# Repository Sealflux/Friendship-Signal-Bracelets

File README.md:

# Friendship-Signal-Bracelets
Friendship Signal Bracelets, which as the name suggests, light up when a bestie is nearby.
## Built for Macondo Hack Club
# Description
Two (or more) bracelets that light up, vibrate, and/or display a pattern when they come within ~3-5 meters of each other, using BLE (Bluetooth Low Energy) RSSI-based proximity detection.

## Features
- Proximity Detection - BLE RSSI(Bluetooth Low Energy Received Signal Strength Indicator) to detect nearby besties
- Cool lights(6 LEDs) when your bestie is nearby
- OLED Display(You can see which bestie is nearby!)
- Audio beeping(Buzzer) when your friend is nearby
- Microphone

## Hardware
- Seeed Xiao ESP32-C3
- SSD1306 0.96" OLED
- WS2812B-V6 LEDs
- ICS-43434 Mems Microphone
- ISM303DACTR Accelerometer
- SPX3819M5-L-1-8 LDO
- LSF0108PWR Level Shifter
- 250mAh LiPo Battery

## Bill of Materials (BOM)

| Designator | Part | Qty | Cost (each) | Total | Link | LCSC # |
|------------|------|:---:|------------|-------|------|--------|
| U1 | Seeed Xiao ESP32-C3 | 1 | $4.99 | $4.99 | https://www.seeedstudio.com/Seeed-XIAO-ESP32C3-p-5431.html | N/A |
| U2 | SSD1306 0.96" OLED | 1 | $2.24 | $2.24 | https://www.lcsc.com/product-detail/C5248080.html | C5248080 |
| SW1 | Tactile Push Button | 1 | $0.56 | $0.56 | https://www.lcsc.com/product-detail/C2888493.html | C2888493 |
| BT1 | LiPo 250mAh Battery | 1 | $8.99 | $8.99 | https://www.amazon.com/EEMB-Battery-Rechargeable-Lithium-Connector/dp/B08FD3V6TF | N/A |
| PCB | PCB Board | 5 | $0.80 | $4 | https://www.jlcpcb.com | N/A |
| C1,C2,C3 | 100nF Capacitor | 3 | $0.0086 | $0.86(Min order of 100) | https://www.lcsc.com/product-detail/C60474.html | C60474 |
| C4 | 220nF Capacitor | 1 | $0.0238 | $1.19(Min order of 100) | https://www.lcsc.com/product-detail/C64705.html | C64705 |
| C5 | 10µF Capacitor | 1 | $0.0372 | $0.74(Min order of 20) | https://www.lcsc.com/product-detail/C192100.html | C192100 |
| C6 | 10nF Capacitor | 1 | $0.016 | $0.8(Min order of 50)| https://www.lcsc.com/product-detail/C100042.html | C100042 |
| LED1-6 | WS2812B-V6 LED | 6 | $0.1011 | $1.01(Multiple order of 5s) | https://www.lcsc.com/product-detail/C52917433.html | C52917433 |
| R1 | 100kΩ Resistor | 1 | $0.0061 | $0.62(Min order of 100) | https://www.lcsc.com/product-detail/C60491.html | C60491 |
| U3 | ICS-43434 Microphone | 1 | $4.66 | $4.66 | https://www.lcsc.com/product-detail/C5656610.html | C5656610 |
| U4 | ISM303DACTR Accelerometer | 1 | $4.04 | $4.04 | https://www.lcsc.com/product-detail/C2913653.html | C2913653 |
| U5 | SPX3819M5-L-1-8 Voltage Regulator | 1 | $0.1437 | $0.72(Min order of 5) | https://www.lcsc.com/product-detail/C24639.html | C24639 |
| U6 | LSF0108PWR Level Shifter | 1 | $0.5849 | $0.5849 | https://www.lcsc.com/product-detail/C190219.html | C190219 |
| BUZZER1 | 1207-P6.5MM Buzzer | 1 | $0.0317 | $0.32(Min order of 10) | https://www.lcsc.com/product-detail/C49246964.html | C49246964 |
| Shipping | N/A | 1 | Seeed($6.5) + LCSC($9.58) + Amazon($7.95) + JLCPCB($3.12) | N/A | N/A | N/A
| Total Costs | N/A | 1 | 11.49+16.94+7.12+27.98 | $63.53 | N/A | N/A |

## Firmware
Basic functional firmware in `/firmware/friendship_bracelet.ino`.
## Steps To Reproduce
1. Order all the components from the BOM
2. Download the gerbers.zip from Production folder and order a pcb from whatever manufacturer(JLCPCB)
3. Solder the components onto the PCB
4. Download the enclosure from Production folder and print using PETG or TPU
5. Order watch strap adapters
6. Assemble the case, sand down the bottom and top parts and hot glue the together. The PCB will fit snugly
7. Flash the Firmware onto the PCB
8. Now repeat steps 1 and 7 for a second bracelet
9. Enjoy!

## Schematic

## PCB

## PCBA

## Case

## Demo Video

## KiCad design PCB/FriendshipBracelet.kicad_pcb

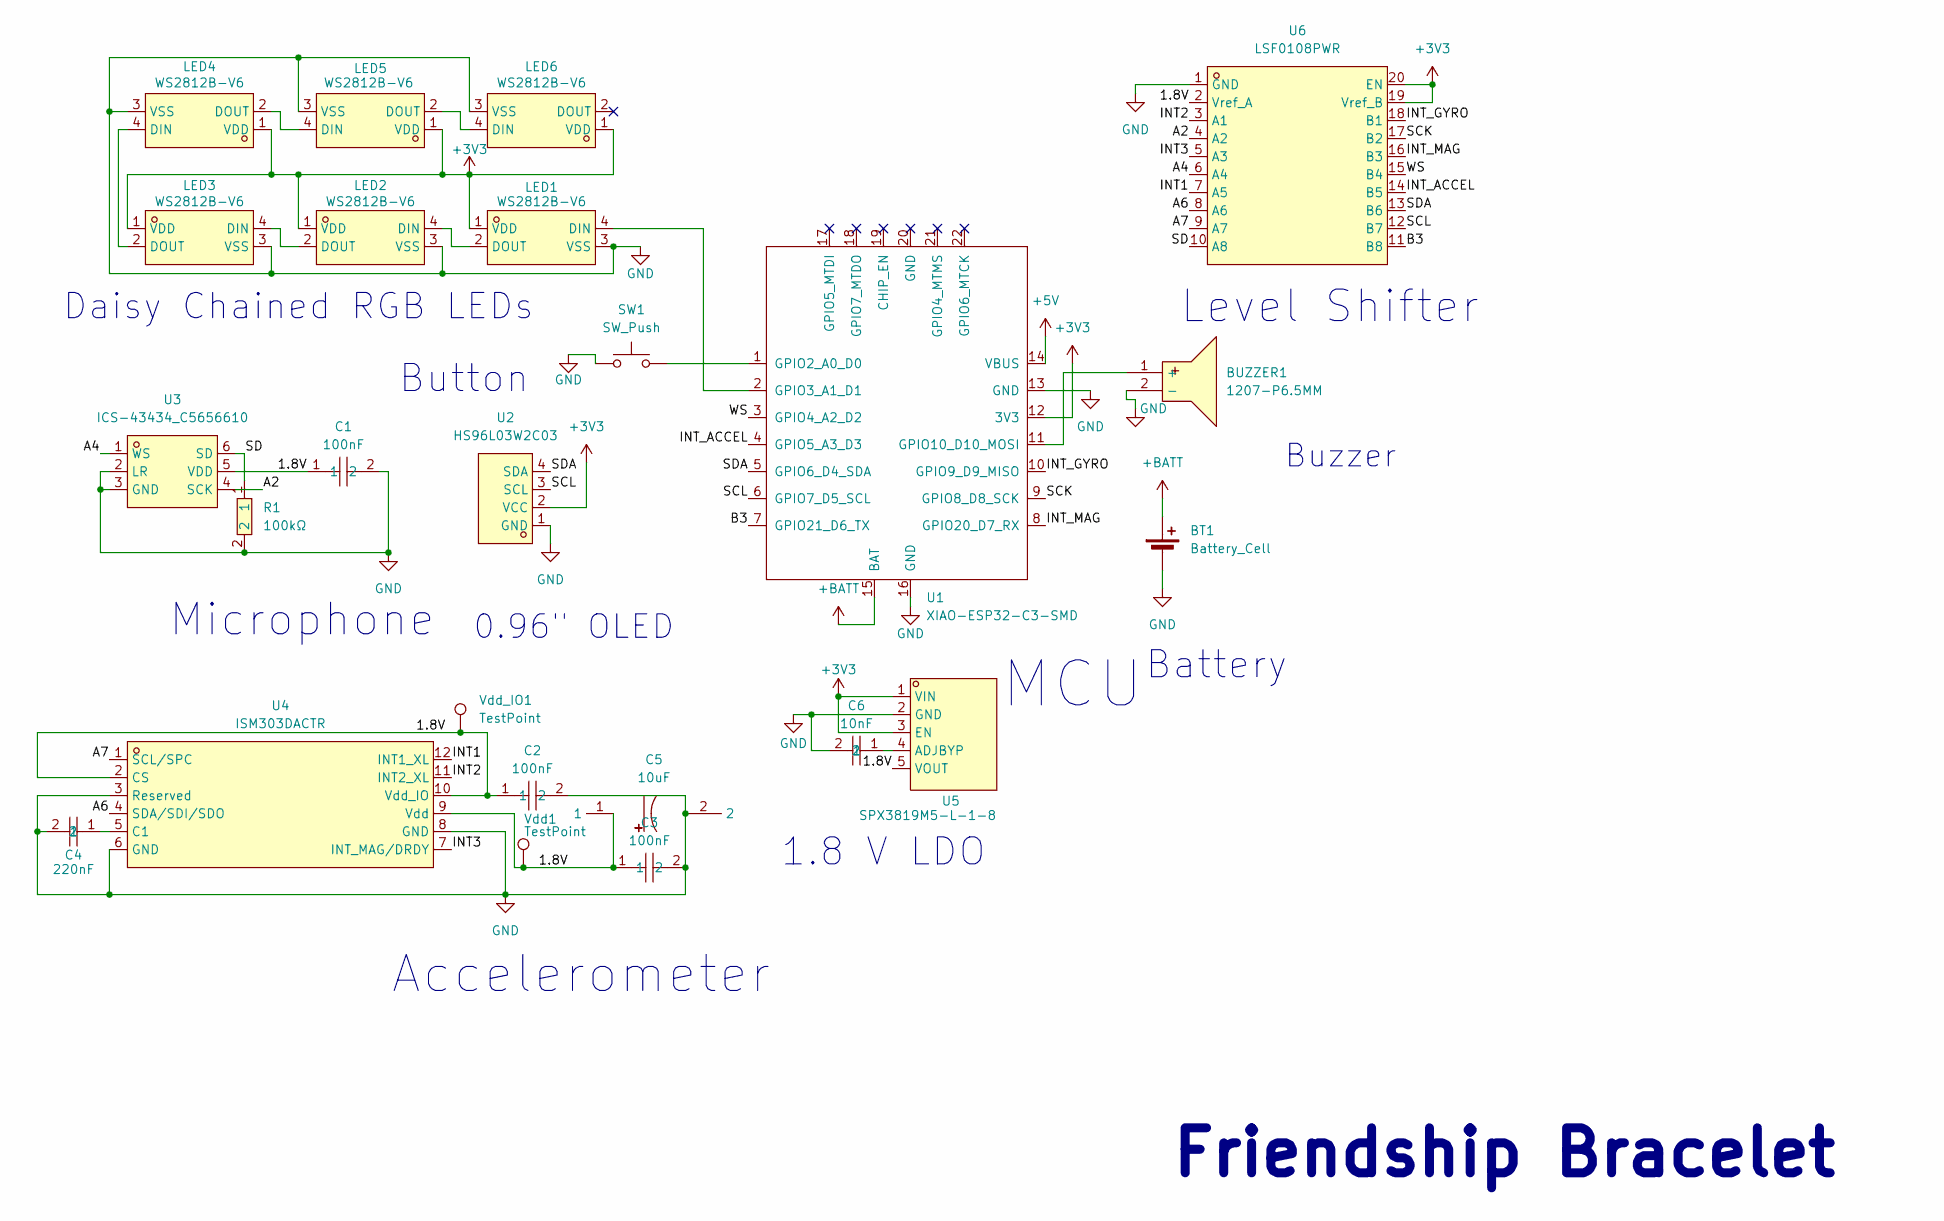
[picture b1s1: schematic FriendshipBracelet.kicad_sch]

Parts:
BT1: Battery_Cell; PinHeader_1x02_P2.54mm_Vertical
BUZZER1: 1207-P6.5MM; BUZ-TH_BD12.5-P6.50-D1.4; MPN 1207-P6.5MM; LCSC Part C49246964
C1, C2, C3: 100nF; C0402; MPN CC0402KRX7R7BB104; LCSC Part C60474
C4: 220nF; C0603; MPN CL10B224KB8NNNC; LCSC Part C64705
C5: 10uF; CAP-TH_BD5.0-P2.00-D0.8-FD; MPN ECR1HBK100MLL050011; LCSC Part C192100
C6: 10nF; C0603; MPN CC0603KRX7R9BB103; LCSC Part C100042
LED1, LED2, LED3, LED4, LED5, LED6: WS2812B-V6; LED-SMD_4P-L5.0-W5.0-TL-A; MPN WS2812B-V6; LCSC Part C52917433
R1: 100kΩ; R0402; MPN RC0402FR-07100KL; LCSC Part C60491
SW1: SW_Push; SW-TH_4P-L4.5-W4.5-P3.00-LS4.8
U1: XIAO-ESP32-C3-SMD; XIAO-ESP32-C3-DIP-SMD
U2: HS96L03W2C03; OLED-TH_L27.8-W27.2-P2.54_C9900033791; MPN HS96L03W2C03; LCSC Part C5248080
U3: ICS-43434_C5656610; MIC-SMD_6P-L3.5-W2.7-P0.90-BL; MPN ICS-43434; LCSC Part C5656610
U4: ISM303DACTR; VLGA-12_L2.0-W2.0-P0.50-BL; MPN ISM303DACTR; LCSC Part C2913653
U5: SPX3819M5-L-1-8; SOT-23-5_L3.0-W1.7-P0.95-LS2.8-TL; MPN SPX3819M5-L-1-8/TR; LCSC Part C24639
U6: LSF0108PWR; TSSOP-20_L6.5-W4.4-P0.65-LS6.4-BL; MPN LSF0108PWR; LCSC Part C190219
Vdd1: TestPoint; TestPoint_Pad_D2.5mm
Vdd_IO1: TestPoint; TestPoint_Pad_D2.5mm

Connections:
+3V3: LED1.1 (VDD), LED2.1 (VDD), LED3.1 (VDD), LED4.1 (VDD), LED5.1 (VDD), LED6.1 (VDD), U1.12 (3V3), U2.2 (VCC), U5.1 (VIN), U5.3 (EN), U6.19 (Vref_B), U6.20 (EN)
+5V: U1.14 (VBUS)
+BATT: BT1.1 (+), U1.15 (BAT)
/1.8V: C1.1, C2.1, C3.1, C5.1, U3.5 (VDD), U4.2 (CS), U4.9 (Vdd), U4.10 (Vdd_IO), U5.5 (VOUT), U6.2 (Vref_A), Vdd1.1 (1_1), Vdd_IO1.1 (1_1)
/A2: U3.4 (SCK), U6.4 (A2)
/A4: U3.1 (WS), U6.6 (A4)
/A6: U4.4 (SDA/SDI/SDO), U6.8 (A6)
/A7: U4.1 (SCL/SPC), U6.9 (A7)
/B3: U1.7 (GPIO21_D6_TX), U6.11 (B8)
/INT1: U4.12 (INT1_XL), U6.7 (A5)
/INT2: U4.11 (INT2_XL), U6.3 (A1)
/INT3: U4.7 (INT_MAG/DRDY), U6.5 (A3)
/INT_ACCEL: U1.4 (GPIO5_A3_D3), U6.14 (B5)
/INT_GYRO: U1.10 (GPIO9_D9_MISO), U6.18 (B1)
/INT_MAG: U1.8 (GPIO20_D7_RX), U6.16 (B3)
/SCK: U1.9 (GPIO8_D8_SCK), U6.17 (B2)
/SCL: U1.6 (GPIO7_D5_SCL), U2.3 (SCL), U6.12 (B7)
/SD: R1.1, U3.6 (SD), U6.10 (A8)
/SDA: U1.5 (GPIO6_D4_SDA), U2.4 (SDA), U6.13 (B6)
/WS: U1.3 (GPIO4_A2_D2), U6.15 (B4)
GND: BT1.2 (-), BUZZER1.2 (-), C1.2, C2.2, C3.2, C4.2, C5.2, C6.2, LED1.3 (VSS), LED2.3 (VSS), LED3.3 (VSS), LED4.3 (VSS), LED5.3 (VSS), LED6.3 (VSS), R1.2, SW1.1, U1.13 (GND), U1.16 (GND), U2.1 (GND), U3.2 (LR), U3.3 (GND), U4.3 (Reserved), U4.6 (GND), U4.8 (GND), U5.2 (GND), U6.1 (GND)
unnamed: BUZZER1.1 (+), U1.11 (GPIO10_D10_MOSI)
unnamed: LED1.4 (DIN), U1.2 (GPIO3_A1_D1)
unnamed: LED1.2 (DOUT), LED2.4 (DIN)
unnamed: LED2.2 (DOUT), LED3.4 (DIN)
unnamed: LED3.2 (DOUT), LED4.4 (DIN)
unnamed: LED4.2 (DOUT), LED5.4 (DIN)
unnamed: LED5.2 (DOUT), LED6.4 (DIN)
unnamed: SW1.2, U1.1 (GPIO2_A0_D0)
unnamed: C4.1, U4.5 (C1)
unnamed: C6.1, U5.4 (ADJBYP)

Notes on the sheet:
Button
MCU
Accelerometer
Microphone
0.96{dblquote} OLED
Daisy Chained RGB LEDs
Battery
Friendship Bracelet
Level Shifter
Buzzer
1.8 V LDO

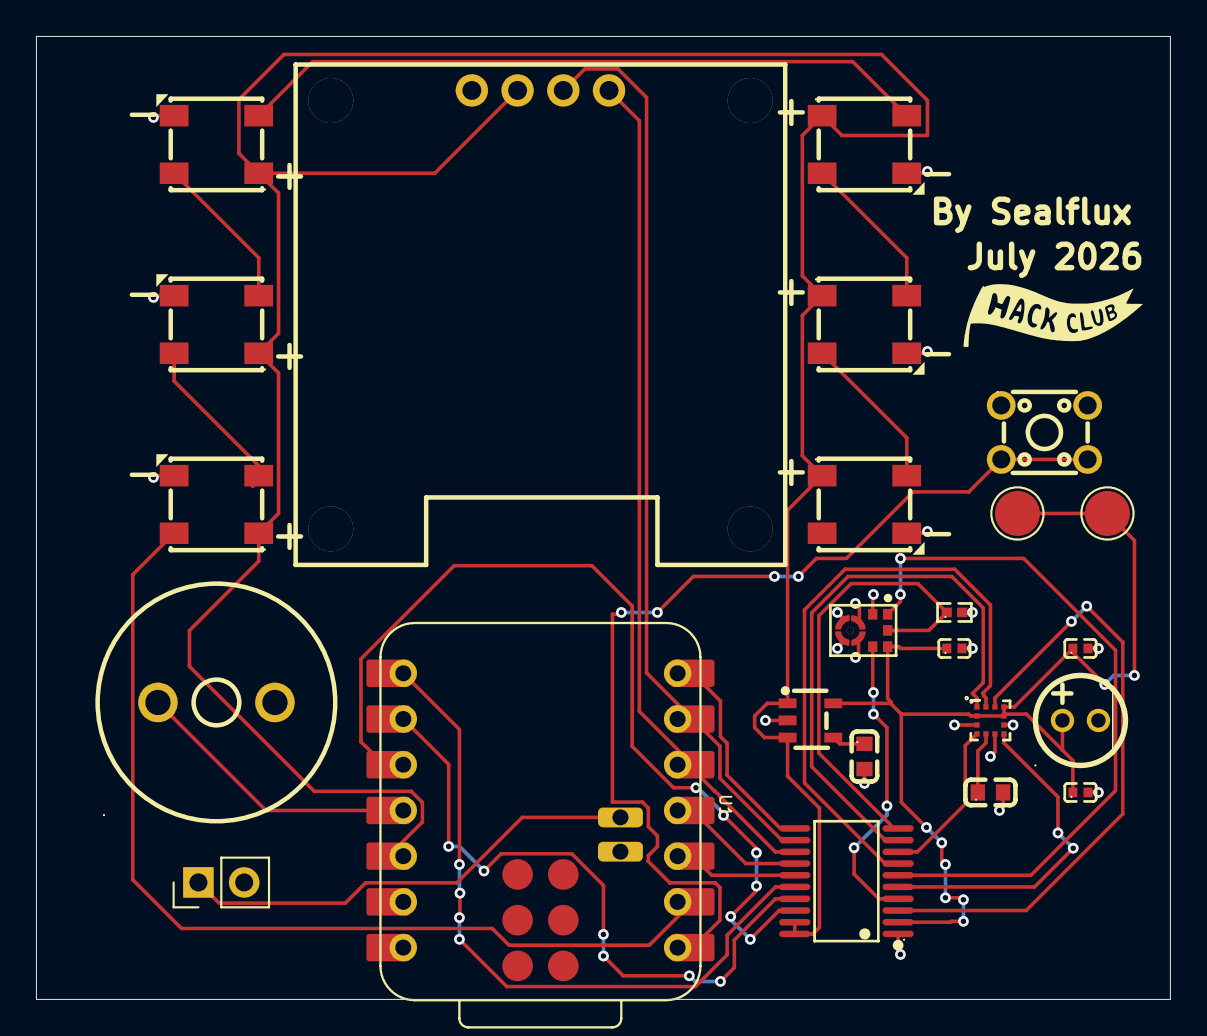
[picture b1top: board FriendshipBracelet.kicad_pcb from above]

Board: 2 copper layers, 63.0 x 53.5 mm, 24 parts (0 on the bottom side), 30 nets.

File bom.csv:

Designator,Part,Qty,Cost (each),Total,Link,LCSC #
U1,Seeed Xiao ESP32-C3,1,$4.99,$4.99,https://www.seeedstudio.com/Seeed-XIAO-ESP32C3-p-5431.html,N/A
U2,SSD1306 0.96" OLED,1,$2.24,$2.24,https://www.lcsc.com/product-detail/C5248080.html,C5248080
SW1,Tactile Push Button,1,$0.56,$0.56,https://www.lcsc.com/product-detail/C2888493.html,C2888493
BT1,LiPo 250mAh Battery,1,$8.99,$8.99,https://www.amazon.com/EEMB-Battery-Rechargeable-Lithium-Con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,N/A
PCB,PCB Board,5,$0.80,$4,https://www.jlcpcb.com,N/A
C1,C2,C3,100nF Capacitor,3,$0.0086,$0.86 (Min order of 100),https://www.lcsc.com/product-detail/C60474.html,C60474
C4,220nF Capacitor,1,$0.0238,$1.19 (Min order of 100),https://www.lcsc.com/product-detail/C64705.html,C64705
C5,10µF Capacitor,1,$0.0372,$0.74 (Min order of 20),https://www.lcsc.com/product-detail/C192100.html,C192100
C6,10nF Capacitor,1,$0.016,$0.80 (Min order of 50),https://www.lcsc.com/product-detail/C100042.html,C100042
LED1-6,WS2812B-V6 LED,6,$0.1011,$1.01 (Multiple order of 5s),https://www.lcsc.com/product-detail/C52917433.html,C52917433
R1,100kΩ Resistor,1,$0.0061,$0.62 (Min order of 100),https://www.lcsc.com/product-detail/C60491.html,C60491
U3,ICS-43434 Microphone,1,$4.66,$4.66,https://www.lcsc.com/product-detail/C5656610.html,C5656610
U4,ISM303DACTR Accelerometer,1,$4.04,$4.04,https://www.lcsc.com/product-detail/C2913653.html,C2913653
U5,SPX3819M5-L-1-8 Voltage Regulator,1,$0.1437,$0.72 (Min order of 5),https://www.lcsc.com/product-detail/C24639.html,C24639
U6,LSF0108PWR Level Shifter,1,$0.5849,$0.5849,https://www.lcsc.com/product-detail/C190219.html,C190219
BUZZER1,1207-P6.5MM Buzzer,1,$0.0317,$0.32 (Min order of 10),https://www.lcsc.com/product-detail/C49246964.html,C49246964
Shipping,N/A,1,"Seeed($6.5) + LCSC($9.58) + Amazon($7.95) + JLCPCB($3.12)",Sum after I calculate,N/A,N/A
Total Costs,N/A,1,"11.49 + 16.94 + 7.12 + 27.98",$63.53,N/A,N/A

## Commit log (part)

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2026-06-27 Skeleton Framework
2026-06-28 Added Journals
